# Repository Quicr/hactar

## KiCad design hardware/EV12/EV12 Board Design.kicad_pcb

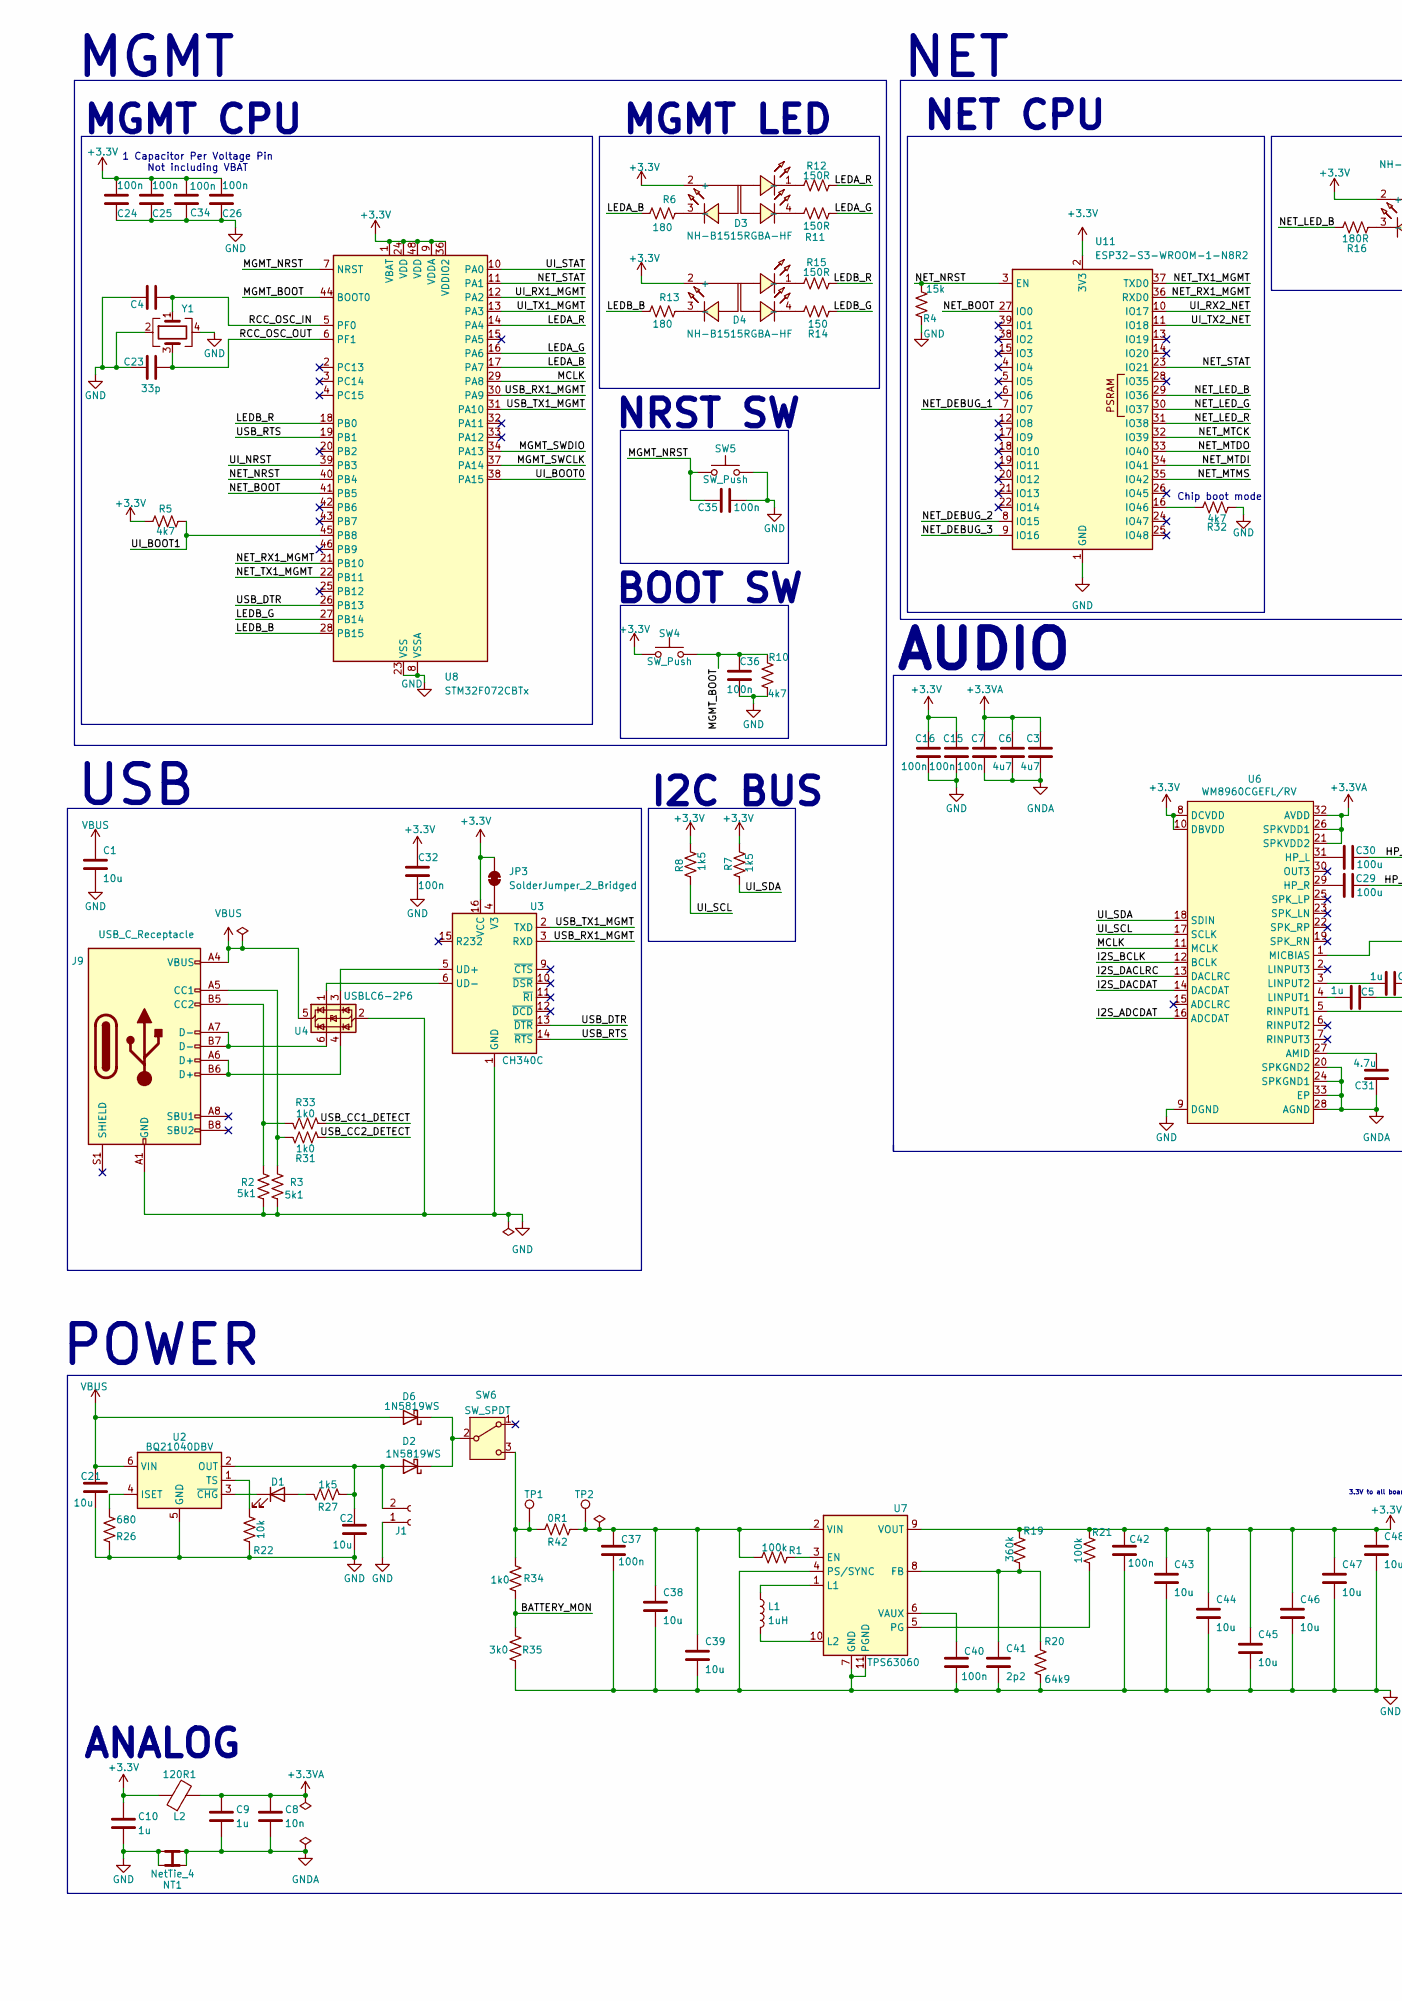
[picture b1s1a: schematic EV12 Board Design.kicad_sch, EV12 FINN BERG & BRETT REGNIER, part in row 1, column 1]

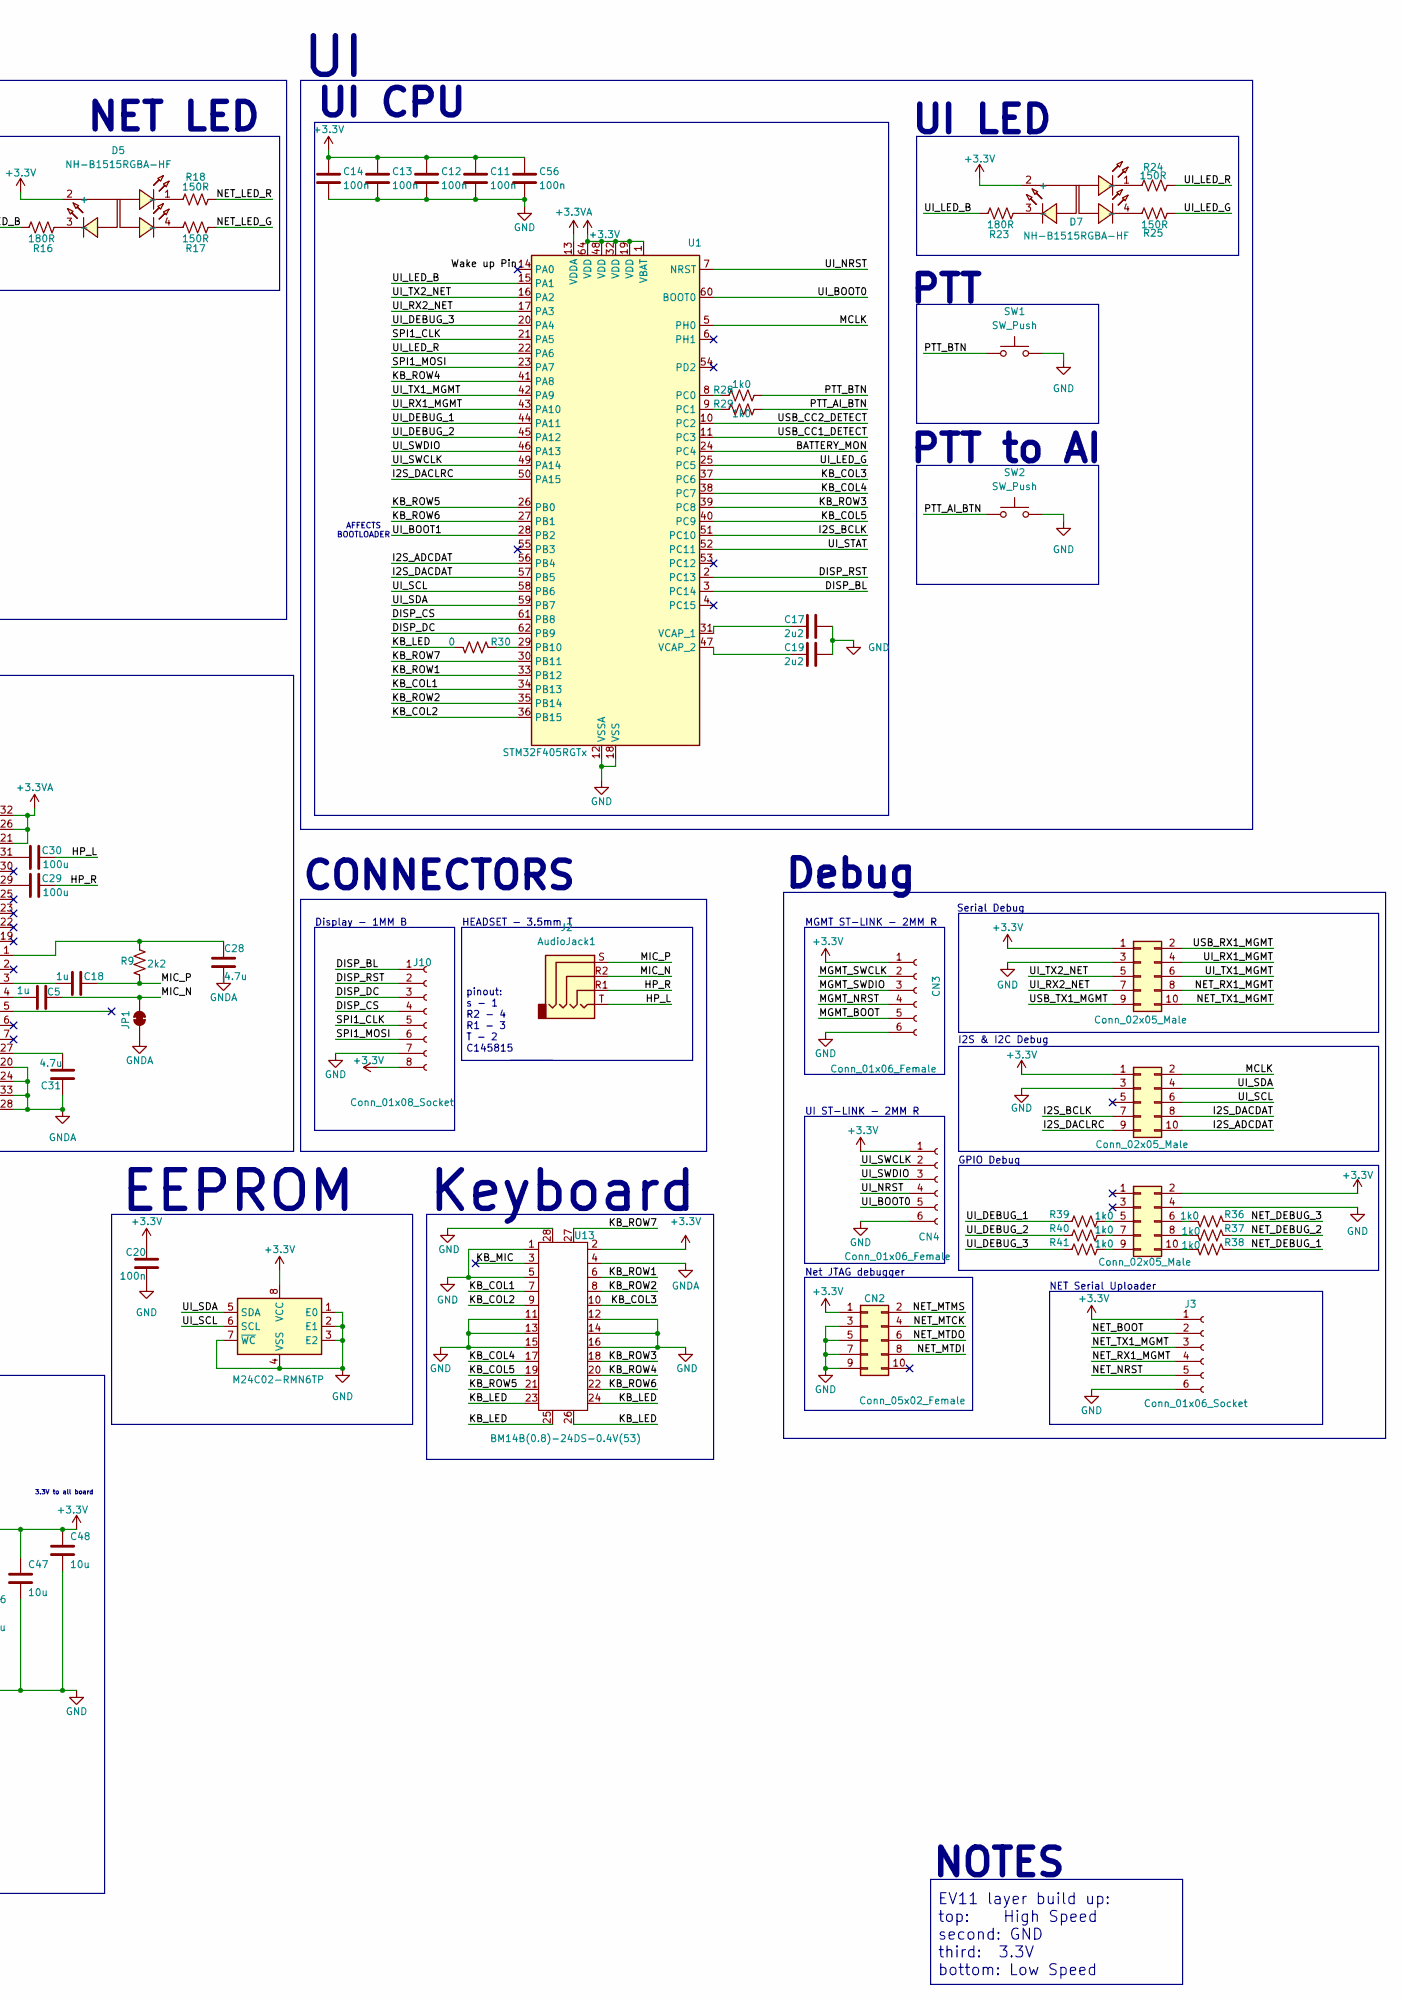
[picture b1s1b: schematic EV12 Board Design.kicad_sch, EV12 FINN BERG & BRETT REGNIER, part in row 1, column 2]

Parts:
C1, C2, C21: 10u; C_0402_1005Metric; JLCPCB Part # C307415
C3, C6: 4u7; C_0402_1005Metric; JLCPCB Part # C23733
C4, C23: 33p; C_0805_2012Metric; JLCPCB Part # C107115
C5, C9, C10, C18: 1u; C_0402_1005Metric; JLCPCB Part # C52923
C7, C11, C12, C13, C14, C15, C16, C20, C24, C25, C26, C32, C34, C35, C36, C56: 100n; C_0402_1005Metric; JLCPCB Part # C1525
C8: 10n; C_0402_1005Metric; JLCPCB Part # C15195
C17, C19: 2u2; C_0402_1005Metric; JLCPCB Part # C12530
C28, C31: 4.7u; C_0402_1005Metric; JLCPCB Part # C23733
C29, C30: 100u; C_1206_3216Metric; JLCPCB Part # C15008
C37, C40, C42: 100n; C_0805_2012Metric; JLCPCB Part # C85866
C38, C39, C43, C44, C45, C46, C47, C48: 10u; C_0805_2012Metric; JLCPCB Part # C83061
C41: 2p2; C_0805_2012Metric; JLCPCB Part # C519933
CN2: Conn_05x02_Female; IDC-SMD_10P-P1.27_X1270WVS-2X05B-6TV01; JLCPCB Part # C2962222
CN3, CN4: Conn_01x06_Female; JST_SH_BM06B-SRSS-TB_1x06-1MP_P1.00mm_Vertical; JLCPCB Part # C3029336
CN5, CN6, CN7: Conn_02x05_Male; IDC-SMD_10P-P1.27_X1270WVS-2X05B-6TV01; JLCPCB Part # C2962222
D1: LED; D_0805_2012Metric; JLCPCB Part # C130114
D2, D6: 1N5819WS; D_SOD-323; JLCPCB Part # C191023
D3, D4, D5, D7: NH-B1515RGBA-HF; LED-ARRAY-SMD_4P-L1.6-W1.5-TL_NH-B1515RGBA; JLCPCB Part # C2874115
J1: Conn_01x02_Socket; JST_PH_S2B-PH-SM4-TB_1x02-1MP_P2.00mm_Horizontal; JLCPCB Part # C295747
J2: AudioJack1; Jack_3.5mm_PJ320D_Horizontal; JLCPCB Part # C431535
J3: Conn_01x06_Socket; JST_SH_BM06B-SRSS-TB_1x06-1MP_P1.00mm_Vertical; JLCPCB Part # C3029336
J9: USB_C_Receptacle; USB_C_Receptacle_HRO_TYPE-C-31-M-12; JLCPCB Part # C165948
J10: Conn_01x08_Socket; JST_SHL_SM08B-SHLS-TF_1x08-1MP_P1.00mm_Horizontal; JLCPCB Part # C3029347
JP1: SolderJumper_2_Bridged; NetTie-2_SMD_Pad0.5mm
JP3: SolderJumper_2_Bridged; SolderJumper-2_P1.3mm_Bridged_RoundedPad1.0x1.5mm
L1: 1uH; MCL2016A1R0MT; JLCPCB Part # C370013
L2: 120R1; L_0603_1608Metric; JLCPCB Part # C127301
NT1: NetTie_4; NetTie-4_SMD_Pad0.5mm
R1, R21: 100k; R_0402_1005Metric; JLCPCB Part # C25741
R2, R3: 5k1; R_0402_1005Metric; JLCPCB Part # C25905
R4: 15k; R_0402_1005Metric; JLCPCB Part # C25756
R5, R10, R32: 4k7; R_0402_1005Metric; JLCPCB Part # C25900
R6, R13: 180; R_0402_1005Metric; JLCPCB Part # C25087
R7, R8, R27: 1k5; R_0402_1005Metric; JLCPCB Part # C25867
R9: 2k2; R_0402_1005Metric; JLCPCB Part # C25879
R11, R12, R15, R17, R18, R24, R25: 150R; R_0402_1005Metric; JLCPCB Part # C25082
R14: 150; R_0402_1005Metric; JLCPCB Part # C25082
R16, R23: 180R; R_0402_1005Metric; JLCPCB Part # C25087
R19: 360k; R_0402_1005Metric; JLCPCB Part # C45956
R20: 64k9; R_0402_1005Metric; JLCPCB Part # C26984
R22: 10k; R_0402_1005Metric; JLCPCB Part # C25744
R26: 680; R_0402_1005Metric; JLCPCB Part # C25130
R28, R29, R31, R33, R34, R36, R37, R38, R39, R40, R41: 1k0; R_0402_1005Metric; JLCPCB Part # C11702
R30: 0; R_0402_1005Metric; JLCPCB Part # C17168
R35: 3k0; R_0402_1005Metric; JLCPCB Part # C25784
R42: 0R1; R_0603_1608Metric; JLCPCB Part # C111027
SW1, SW2: SW_Push; SW-SMD_L7.5-W8.0-P4.50_TS-1045-A13B3-D2; JLCPCB Part # C557898
SW4, SW5: SW_Push; SW_DIP_SPSTx01_Slide_6.7x4.1mm_W6.73mm_P2.54mm_LowProfile_J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; JLCPCB Part # C266189
SW6: SW_SPDT; SW-TH_SS-12D11G5R; JLCPCB Part # C388633
TP1, TP2: TestPoint; TestPoint_THTPad_D1.5mm_Drill0.7mm
U1: STM32F405RGTx; LQFP-64_10x10mm_P0.5mm; JLCPCB Part # C15742
U2: BQ21040DBV; SOT-23-6; JLCPCB Part # C202311
U3: CH340C; SOIC-16_3.9x9.9mm_P1.27mm; JLCPCB Part # C84681
U4: USBLC6-2P6; SOT-666; JLCPCB Part # C2827693
U5: M24C02-RMN6TP; SOIC-8_3.9x4.9mm_P1.27mm; JLCPCB Part # C83836
U6: WM8960CGEFL/RV; QFN-32-1EP_5x5mm_P0.5mm_EP3.45x3.45mm_ThermalVias; JLCPCB Part # C18752
U7: TPS63060; Texas_S-PWSON-N10_ThermalVias; JLCPCB Part # C48567
U8: STM32F072CBTx; LQFP-48_7x7mm_P0.5mm; JLCPCB Part # C80488
U11: ESP32-S3-WROOM-1-N8R2; ESP32-S3-WROOM-1U; JLCPCB Part # C3013944
U13: BM14B(0.8)-24DS-0.4V(53); BM14B(0.B)-24DS-0.4V(53); JLCPCB Part # C9900001863
Y1: Crystal_GND24; Crystal_SMD_3225-4Pin_3.2x2.5mm; JLCPCB Part # C13738

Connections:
+3.3V: C10.1, C11.1, C12.1, C13.1, C14.1, C15.2, C16.2, C20.2, C24.2, C25.2, C26.2, C32.1, C34.2, C42.1, C43.1, C44.1, C45.1, C46.1, C47.1, C48.1, C56.1, CN2.1, CN3.1, CN4.1, CN5.1, CN6.1, CN7.2, D3.2 (+), D4.2 (+), D5.2 (+), D7.2 (+), J3.1, J10.8, JP3.2 (B), L2.1, R5.1, R7.1, R8.1, R19.2, R21.2, SW4.1, U1.1 (VBAT), U1.19 (VDD), U1.32 (VDD), U1.48 (VDD), U1.64 (VDD), U3.16 (VCC), U5.8 (VCC), U6.8 (DCVDD), U6.10 (DBVDD), U7.9 (VOUT), U8.1 (VBAT), U8.9 (VDDA), U8.24 (VDD), U8.36 (VDDIO2), U8.48 (VDD), U11.2 (3V3), U13.2
+3.3VA: C3.1, C6.1, C7.2, C8.1, C9.1, L2.2, U1.13 (VDDA), U6.21 (SPKVDD2), U6.26 (SPKVDD1), U6.32 (AVDD)
/BATTERY_MON: R34.1, R35.2, U1.24 (PC4)
/DISP_BL: J10.1, U1.3 (PC14)
/DISP_CS: J10.4, U1.61 (PB8)
/DISP_DC: J10.3, U1.62 (PB9)
/DISP_RST: J10.2, U1.2 (PC13)
/HP_L: C30.2, J2.T
/HP_R: C29.2, J2.R1
/I2S_ADCDAT: CN5.10, U1.56 (PB4), U6.16 (ADCDAT)
/I2S_BCLK: CN5.7, U1.51 (PC10), U6.12 (BCLK)
/I2S_DACDAT: CN5.8, U1.57 (PB5), U6.14 (DACDAT)
/I2S_DACLRC: CN5.9, U1.50 (PA15), U6.13 (DACLRC)
/KB_COL1: U1.34 (PB13), U13.7
/KB_COL2: U1.36 (PB15), U13.9
/KB_COL3: U1.37 (PC6), U13.10
/KB_COL4: U1.38 (PC7), U13.17
/KB_COL5: U1.40 (PC9), U13.19
/KB_LED: R30.2, U13.23, U13.24, U13.25, U13.26
/KB_MIC: U13.3
/KB_ROW1: U1.33 (PB12), U13.6
/KB_ROW2: U1.35 (PB14), U13.8
/KB_ROW3: U1.39 (PC8), U13.18
/KB_ROW4: U1.41 (PA8), U13.20
/KB_ROW5: U1.26 (PB0), U13.21
/KB_ROW6: U1.27 (PB1), U13.22
/KB_ROW7: U1.30 (PB11), U13.27
/LEDA_B: R6.2, U8.17 (PA7)
/LEDA_G: R11.2, U8.16 (PA6)
/LEDA_R: R12.2, U8.14 (PA4)
/LEDB_B: R13.2, U8.28 (PB15)
/LEDB_G: R14.2, U8.27 (PB14)
/LEDB_R: R15.2, U8.18 (PB0)
/MCLK: CN5.2, U1.5 (PH0), U6.11 (MCLK), U8.29 (PA8)
/MGMT_BOOT: C36.2, CN3.5, R10.2, SW4.2, U8.44 (BOOT0)
/MGMT_NRST: C35.1, CN3.4, SW5.2, U8.7 (NRST)
/MGMT_SWCLK: CN3.2, U8.37 (PA14)
/MGMT_SWDIO: CN3.3, U8.34 (PA13)
/MIC_N: C5.2, J2.R2, JP1.1 (A)
/MIC_P: C18.2, J2.S, R9.1
/NET_BOOT: J3.2, U8.41 (PB5), U11.27 (IO0)
/NET_DEBUG_1: R38.1, U11.7 (IO7)
/NET_DEBUG_2: R37.1, U11.8 (IO15)
/NET_DEBUG_3: R36.1, U11.9 (IO16)
/NET_LED_B: R16.1, U11.29 (IO36)
/NET_LED_G: R17.1, U11.30 (IO37)
/NET_LED_R: R18.1, U11.31 (IO38)
/NET_MTCK: CN2.4, U11.32 (IO39)
/NET_MTDI: CN2.8, U11.34 (IO41)
/NET_MTDO: CN2.6, U11.33 (IO40)
/NET_MTMS: CN2.2, U11.35 (IO42)
/NET_NRST: J3.5, R4.1, U8.40 (PB4), U11.3 (EN)
/NET_RX1_MGMT: CN6.8, J3.4, U8.21 (PB10), U11.36 (RXD0)
/NET_STAT: U8.11 (PA1), U11.23 (IO21)
/NET_TX1_MGMT: CN6.10, J3.3, U8.22 (PB11), U11.37 (TXD0)
/PTT_AI_BTN: R29.2, SW2.1
/PTT_BTN: R28.2, SW1.1
/RCC_OSC_IN: C4.2, U8.5 (PF0), Y1.1
/RCC_OSC_OUT: C23.2, U8.6 (PF1), Y1.3
/SPI1_CLK: J10.5, U1.21 (PA5)
/SPI1_MOSI: J10.6, U1.23 (PA7)
/UI_BOOT0: CN4.5, U1.60 (BOOT0), U8.38 (PA15)
/UI_BOOT1: R5.2, U1.28 (PB2), U8.45 (PB8)
/UI_DEBUG_1: R39.1, U1.44 (PA11)
/UI_DEBUG_2: R40.1, U1.45 (PA12)
/UI_DEBUG_3: R41.1, U1.20 (PA4)
/UI_LED_B: R23.1, U1.15 (PA1)
/UI_LED_G: R25.1, U1.25 (PC5)
/UI_LED_R: R24.1, U1.22 (PA6)
/UI_NRST: CN4.4, U1.7 (NRST), U8.39 (PB3)
/UI_RX1_MGMT: CN6.4, U1.43 (PA10), U8.12 (PA2)
/UI_RX2_NET: CN6.7, U1.17 (PA3), U11.10 (IO17)
/UI_SCL: CN5.6, R8.2, U1.58 (PB6), U5.6 (SCL), U6.17 (SCLK)
/UI_SDA: CN5.4, R7.2, U1.59 (PB7), U5.5 (SDA), U6.18 (SDIN)
/UI_STAT: U1.52 (PC11), U8.10 (PA0)
/UI_SWCLK: CN4.2, U1.49 (PA14)
/UI_SWDIO: CN4.3, U1.46 (PA13)
/UI_TX1_MGMT: CN6.6, U1.42 (PA9), U8.13 (PA3)
/UI_TX2_NET: CN6.5, U1.16 (PA2), U11.11 (IO18)
/USB_CC1_DETECT: R33.1, U1.11 (PC3)
/USB_CC2_DETECT: R31.1, U1.10 (PC2)
/USB_DTR: U3.13 (~DTR), U8.26 (PB13)
/USB_RTS: U3.14 (~RTS), U8.19 (PB1)
/USB_RX1_MGMT: CN6.2, U3.3 (RXD), U8.30 (PA9)
/USB_TX1_MGMT: CN6.9, U3.2 (TXD), U8.31 (PA10)
/Wake up Pin: U1.14 (PA0)
GND: C1.2, C2.2, C4.1, C10.2, C11.2, C12.2, C13.2, C14.2, C15.1, C16.1, C17.1, C19.1, C20.1, C21.2, C23.1, C24.1, C25.1, C26.1, C32.2, C34.1, C35.2, C36.1, C37.2, C38.2, C39.2, C40.2, C41.2, C42.2, C43.2, C44.2, C45.2, C46.2, C47.2, C48.2, C56.2, CN2.3, CN2.5, CN2.7, CN2.9, CN3.6, CN4.6, CN5.3, CN6.3, CN7.4, J1.1, J3.6, J9.A1 (GND), J9.A12 (GND), J9.B1 (GND), J9.B12 (GND), J10.7, NT1.1, NT1.3, R2.1, R3.1, R4.2, R10.1, R20.1, R22.2, R26.2, R32.2, R35.1, SW1.2, SW2.2, SW5.1, U1.12 (VSSA), U1.18 (VSS), U1.63 (VSS), U2.5 (GND), U3.1 (GND), U4.2 (GND), U5.1 (E0), U5.2 (E1), U5.3 (E2), U5.4 (VSS), U5.7 (~WC), U6.9 (DGND), U7.4 (PS/SYNC), U7.7 (GND), U7.11 (PGND), U8.8 (VSSA), U8.23 (VSS), U8.35 (VSS), U8.47 (VSS), U11.1 (GND), U11.40 (GND), U11.41 (GND), U13.1, U13.5, U13.11, U13.12, U13.13, U13.14, U13.15, U13.16, U13.28, Y1.2, Y1.4
GNDA: C3.2, C6.2, C7.1, C8.2, C9.2, C28.2, C31.2, JP1.2 (B), NT1.2, NT1.4, U6.20 (SPKGND2), U6.24 (SPKGND1), U6.28 (AGND), U6.33 (EP), U13.4
unnamed: CN7.5, R39.2
unnamed: CN7.6, R36.2
unnamed: CN7.7, R40.2
unnamed: CN7.8, R37.2
unnamed: CN7.9, R41.2
unnamed: CN7.10, R38.2
unnamed: D1.2 (A), R27.2
unnamed: D1.1 (K), U2.3 (~CHG)
unnamed: C2.1, D2.2 (A), J1.2, R27.1, U2.2 (OUT)
unnamed: D2.1 (K), D6.1 (K), SW6.2 (B)
unnamed: D3.1 (-), R12.1
unnamed: D3.3 (-), R6.1
unnamed: D3.4 (-), R11.1
unnamed: D4.1 (-), R15.1
unnamed: D4.3 (-), R13.1
unnamed: D4.4 (-), R14.1
unnamed: D5.1 (-), R18.2
unnamed: D5.3 (-), R16.2
unnamed: D5.4 (-), R17.2
unnamed: D7.1 (-), R24.2
unnamed: D7.3 (-), R23.2
unnamed: D7.4 (-), R25.2
unnamed: J9.A5 (CC1), R3.2, R31.2
unnamed: J9.B5 (CC2), R2.2, R33.2
unnamed: J9.A6 (D+), J9.B6 (D+), U4.4 (I/O2)
unnamed: J9.A7 (D-), J9.B7 (D-), U4.6 (I/O1)
unnamed: JP3.1 (A), U3.4 (V3)
unnamed: R34.2, R42.1, SW6.3 (C), TP1.1
unnamed: R30.1, U1.29 (PB10)
unnamed: R28.1, U1.8 (PC0)
unnamed: R29.1, U1.9 (PC1)
unnamed: C17.2, U1.31 (VCAP_1)
unnamed: C19.2, U1.47 (VCAP_2)
unnamed: R26.1, U2.4 (ISET)
unnamed: R22.1, U2.1 (TS)
unnamed: U3.5 (UD+), U4.3 (I/O2)
unnamed: U3.6 (UD-), U4.1 (I/O1)
unnamed: C31.1, U6.27 (AMID)
unnamed: C30.1, U6.31 (HP_L)
unnamed: C29.1, U6.29 (HP_R)
unnamed: C5.1, U6.4 (LINPUT1)
unnamed: C18.1, U6.3 (LINPUT2)
unnamed: C28.1, R9.2, U6.1 (MICBIAS)
unnamed: R1.2, U7.3 (EN)
unnamed: C41.1, R19.1, R20.2, U7.8 (FB)
unnamed: L1.1, U7.1 (L1)
unnamed: L1.2, U7.10 (L2)
unnamed: R21.1, U7.5 (PG)
unnamed: C40.1, U7.6 (VAUX)
unnamed: C37.1, C38.1, C39.1, R1.1, R42.2, TP2.1, U7.2 (VIN)
unnamed: R32.1, U11.16 (IO46)
VBUS: C1.1, C21.1, D6.2 (A), J9.A4 (VBUS), J9.A9 (VBUS), J9.B4 (VBUS), J9.B9 (VBUS), U2.6 (VIN), U4.5 (VBUS)

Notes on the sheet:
MGMT
NET CPU
pinout: s - 1 R2 - 4 R1 - 3 T - 2 C145815
Serial Debug
MGMT CPU
PTT to AI
NET
POWER
AFFECTS BOOTLOADER
CONNECTORS
NET LED
UI CPU
UI ST-LINK - 2MM R
HEADSET - 3.5mm T
Chip boot mode
Net JTAG debugger
NET Serial Uploader
NRST SW
EV11 layer build up: top: High Speed second: GND third: 3.3V bottom: Low Speed
Debug
AUDIO
PTT
BOOT SW
EEPROM
I2C BUS
MGMT ST-LINK - 2MM R
USB
MGMT LED
3.3V to all board
NOTES
Keyboard
Display - 1MM B
I2S & I2C Debug
GPIO Debug
1 Capacitor Per Voltage Pin Not including VBAT
UI LED
ANALOG

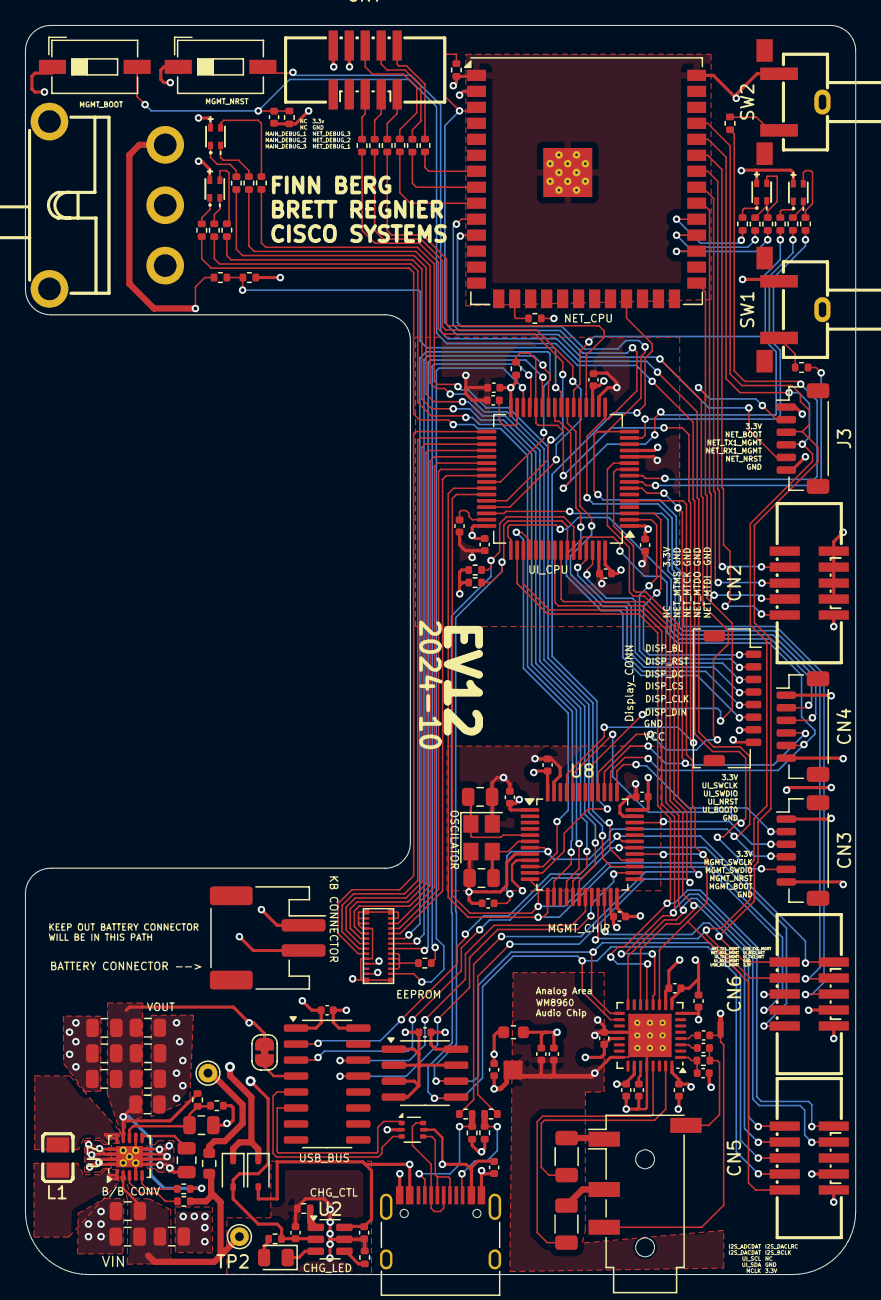
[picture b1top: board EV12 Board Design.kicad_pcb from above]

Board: 4 copper layers, 66.0 x 99.3 mm, 129 parts (0 on the bottom side), 138 nets.

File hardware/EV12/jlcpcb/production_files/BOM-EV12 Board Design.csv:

Comment,Designator,Footprint,LCSC,Quantity
33p,"C23,C4",C_0805_2012Metric,C107115,2
0R1,R42,R_0603_1608Metric,C111027,1
1k0,"R28,R29,R31,R33,R34,R36,R37,R38,R39,R40,R41",R_0402_1005Metric,C11702,11
2u2,"C17,C19",C_0402_1005Metric,C12530,2
120R1,L2,L_0603_1608Metric,C127301,1
LED,D1,D_0805_2012Metric,C130114,1
Crystal_GND24,Y1,Crystal_SMD_3225-4Pin_3.2x2.5mm,C13738,1
100u,"C29,C30",C_1206_3216Metric,C15008,2
10n,C8,C_0402_1005Metric,C15195,1
100n,"C11,C12,C13,C14,C15,C16,C20,C24,C25,C26,C32,C34,C35,C36,C56,C7",C_0402_1005Metric,C1525,16
STM32F405RGTx,U1,LQFP-64_10x10mm_P0.5mm,C15742,1
USB_C_Receptacle,J9,USB_C_Receptacle_HRO_TYPE-C-31-M-12,C165948,1
0,R30,R_0402_1005Metric,C17168,1
WM8960CGEFL/RV,U6,QFN-32-1EP_5x5mm_P0.5mm_EP3.45x3.45mm_ThermalVias,C18752,1
1N5819WS,"D2,D6",D_SOD-323,C191023,2
BQ21040DBV,U2,SOT-23-6,C202311,1
4.7u,"C28,C3,C31,C6",C_0402_1005Metric,C23733,4
150R,"R11,R12,R14,R15,R17,R18,R24,R25",R_0402_1005Metric,C25082,8
180,"R13,R16,R23,R6",R_0402_1005Metric,C25087,4
680,R26,R_0402_1005Metric,C25130,1
100k,"R1,R21",R_0402_1005Metric,C25741,2
10k,R22,R_0402_1005Metric,C25744,1
15k,R4,R_0402_1005Metric,C25756,1
3k0,R35,R_0402_1005Metric,C25784,1
1k5,"R27,R7,R8",R_0402_1005Metric,C25867,3
2k2,R9,R_0402_1005Metric,C25879,1
4k7,"R10,R32,R5",R_0402_1005Metric,C25900,3
5k1,"R2,R3",R_0402_1005Metric,C25905,2
SW_Push,"SW4,SW5",SW_DIP_SPSTx01_Slide_6.7x4.1mm_W6.73mm_P2.54mm_LowProfile_JPin,C266189,2
64k9,R20,R_0402_1005Metric,C26984,1
USBLC6-2P6,U4,SOT-666,C2827693,1
NH-B1515RGBA-HF,"D3,D4,D5,D7",LED-ARRAY-SMD_4P-L1.6-W1.5-TL_NH-B1515RGBA,C2874115,4
Conn_01x02_Socket,J1,JST_PH_S2B-PH-SM4-TB_1x02-1MP_P2.00mm_Horizontal,C295747,1
Conn_05x02_Female,"CN2,CN5,CN6,CN7",IDC-SMD_10P-P1.27_X1270WVS-2X05B-6TV01,C2962222,4
ESP32-S3-WROOM-1-N8R2,U11,ESP32-S3-WROOM-1U,C3013944,1
Conn_01x06_Female,"CN3,CN4,J3",JST_SH_BM06B-SRSS-TB_1x06-1MP_P1.00mm_Vertical,C3029336,3
Conn_01x08_Socket,J10,JST_SHL_SM08B-SHLS-TF_1x08-1MP_P1.00mm_Horizontal,C3029347,1
10u,"C1,C2,C21",C_0402_1005Metric,C307415,3
1uH,L1,MCL2016A1R0MT,C370013,1
SW_SPDT,SW6,SW-TH_SS-12D11G5R,C388633,1
AudioJack1,J2,Jack_3.5mm_PJ320D_Horizontal,C431535,1
360k,R19,R_0402_1005Metric,C45956,1
TPS63060,U7,Texas_S-PWSON-N10_ThermalVias,C48567,1
2p2,C41,C_0805_2012Metric,C519933,1
1u,"C10,C18,C5,C9",C_0402_1005Metric,C52923,4
SW_Push,"SW1,SW2",SW-SMD_L7.5-W8.0-P4.50_TS-1045-A13B3-D2,C557898,2
STM32F072CBTx,U8,LQFP-48_7x7mm_P0.5mm,C80488,1
10u,"C38,C39,C43,C44,C45,C46,C47,C48",C_0805_2012Metric,C83061,8
M24C02-RMN6TP,U5,SOIC-8_3.9x4.9mm_P1.27mm,C83836,1
CH340C,U3,SOIC-16_3.9x9.9mm_P1.27mm,C84681,1
100n,"C37,C40,C42",C_0805_2012Metric,C85866,3
BM14B(0.8)-24DS-0.4V(53),U13,BM14B(0.B)-24DS-0.4V(53),C9900001863,1
